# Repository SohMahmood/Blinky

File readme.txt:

PCB schematic to flash a blinking LED

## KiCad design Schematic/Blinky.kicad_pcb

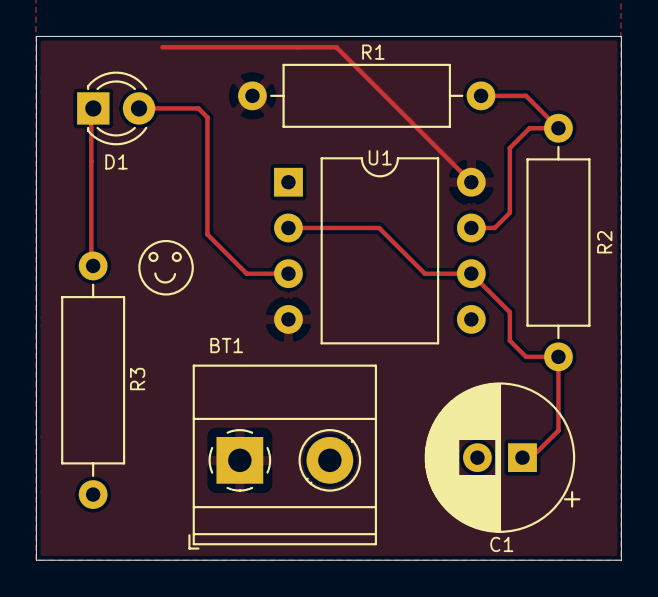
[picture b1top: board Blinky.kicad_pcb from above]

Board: 2 copper layers, 32.5 x 29.1 mm, 7 parts (0 on the bottom side), 6 nets.

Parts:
BT1: Battery_Cell; TerminalBlock_Phoenix_MKDS-1,5-2_1x02_P5.00mm_Horizontal
C1: C; CP_Radial_D8.0mm_P2.50mm
D1: LED; LED_D3.0mm
R1, R3: 1k; R_Axial_DIN0309_L9.0mm_D3.2mm_P12.70mm_Horizontal
R2: 470k; R_Axial_DIN0309_L9.0mm_D3.2mm_P12.70mm_Horizontal
U1: NE555P; DIP-8_W10.16mm

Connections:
/OUT: D1.2, U1.3
/TRIG: C1.1, R2.2, U1.2, U1.6
/VCC: BT1.1, R1.1, U1.4, U1.8
GND: BT1.2, C1.2, R3.2, U1.1
unnamed: D1.1, R3.1
unnamed: R1.2, R2.1, U1.7

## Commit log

2021-02-02 Blinky files
